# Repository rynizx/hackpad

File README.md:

# hackpad

Stardance 2026 challenge project! :3
this is my little  hackpad for my own sillies and tinkerintg with for the stardance 26 challange :3

## how to use said files that are here

its nowhere near done but just open kicad and explode :p

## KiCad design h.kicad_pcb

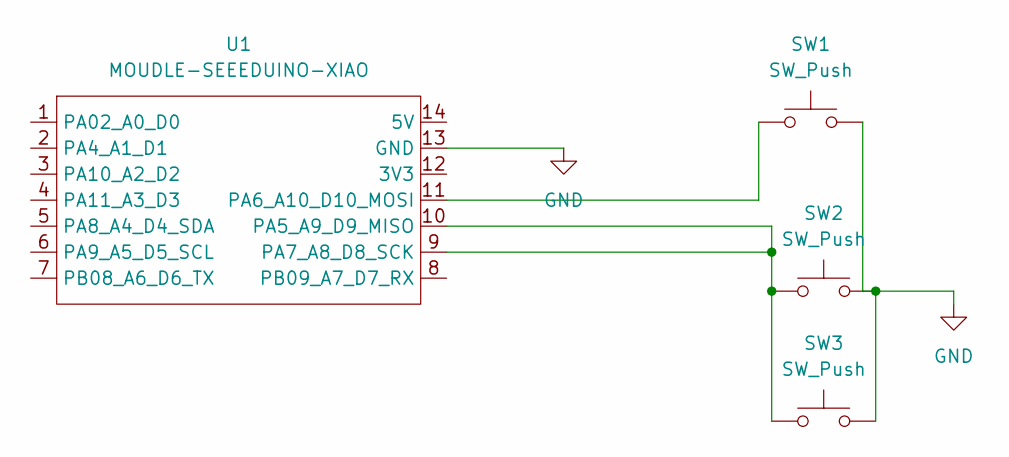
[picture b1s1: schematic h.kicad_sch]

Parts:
SW1, SW2, SW3: SW_Push; SW_Cherry_MX_1.00u_PCB
U1: MOUDLE-SEEEDUINO-XIAO; XIAO-Generic-Hybrid-14P-2.54-21X17.8MM

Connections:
GND: SW1.2, SW2.2, SW3.2, U1.13 (GND)
unnamed: SW2.1, SW3.1, U1.9 (PA7_A8_D8_SCK), U1.10 (PA5_A9_D9_MISO)
unnamed: SW1.1, U1.11 (PA6_A10_D10_MOSI)

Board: 2 copper layers, 4 parts (0 on the bottom side), 3 nets, no tracks yet.

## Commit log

2026-06-06 the start..?
2026-06-06 okay
2026-06-06 and once more
